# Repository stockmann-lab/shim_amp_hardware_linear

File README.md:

# MGH open-source shim amplifier repo. 

This repo contains files related to the MGH "Revision D" linear amplifier development (and associated projects).  The shim amplifiers are designed to drive stable currents (up to 4A/channel or more if channels are ganged together in parallel) in shim coils and other inductive loads used for MRI research experiments.  The amplifiers are designed to operate inside the MRI shielded room without causing image degradation due to RF interference.

Content will include design files and bills of materials for both the Printed Circuit Boards (power board, control board, and power distribution board) as well as the mechanical enclosure.

The software and firmware for controlling the shim amplifiers via a Snickerdoodle device can be built from [https://github.com/LincolnCB/rev_d_shim](https://github.com/LincolnCB/rev_d_shim) using the [https://github.com/LincolnCB/zynq_toolbox](https://github.com/LincolnCB/zynq_toolbox) build environment repo.

More details forthcoming.

## Previous shim amplifier projects 

This project builds upon previous work done at MIT-MGH on a Class-AB linear shim amplifier that uses OPA549 op amps in a push-pull configuration.  This previous "Revision C" shim amplifier design is available at:

https://rflab.martinos.org/index.php?title=Current_driver:Current_driver

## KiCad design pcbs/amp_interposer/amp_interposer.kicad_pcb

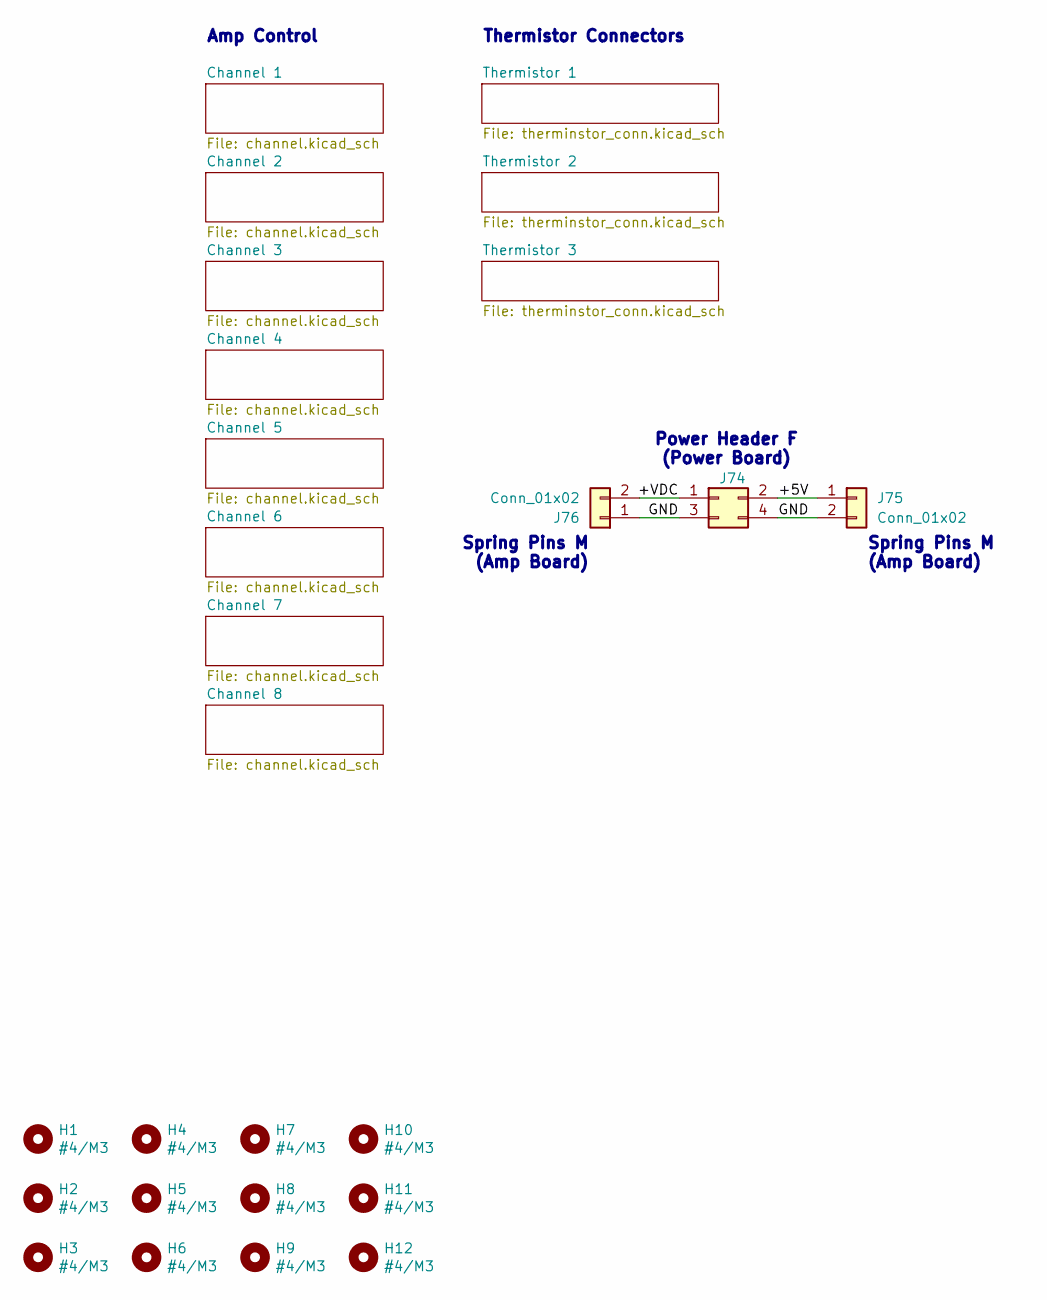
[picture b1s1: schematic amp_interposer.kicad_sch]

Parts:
H1, H2, H3, H4, H5, H6, H7, H8, H9, H10, H11, H12: #4/M3; MountingHole_3.2mm_M3
J74: Conn_02x02; PinSocket_2x02_P2.54mm_Vertical_SMD_BotEntry_Pin; MPN M20-7810245 / M20-7810245R
J75, J76: Conn_01x02; Conn_70AAJ-M_SIB_1x02_P2.54mm_M

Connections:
/+5V: J74.2, J75.1
/+VDC: J74.1, J76.2
/GND: J74.3, J74.4, J75.2, J76.1

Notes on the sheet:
Spring Pins M (Amp Board)
Power Header F (Power Board)
Thermistor Connectors
Amp Control

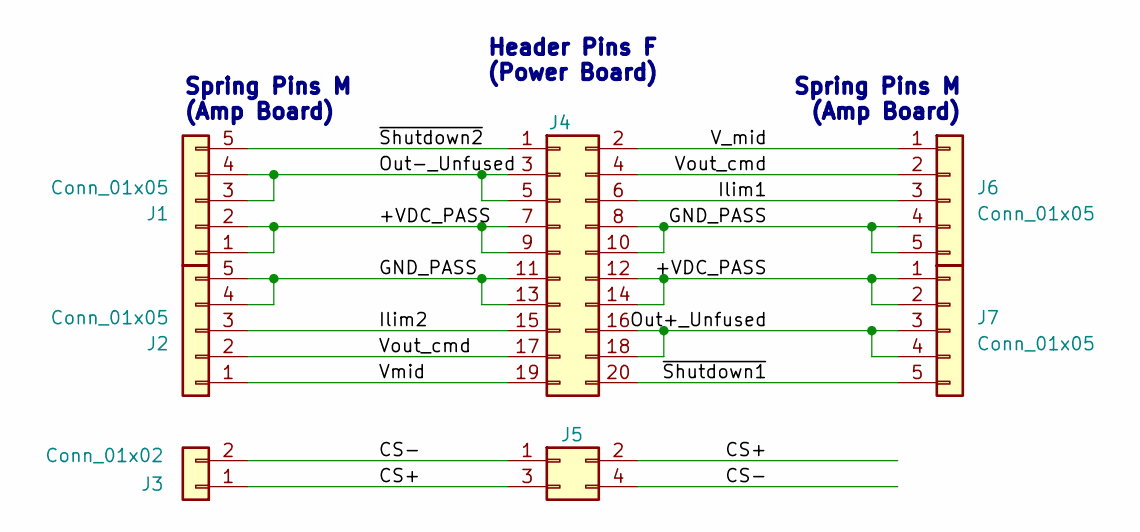
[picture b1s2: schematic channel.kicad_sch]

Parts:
J1, J2, J6, J7: Conn_01x05; Conn_70AAJ-M_SIB_1x05_P2.54mm_M
J3: Conn_01x02; Conn_70AAJ-M_SIB_1x02_P2.54mm_M
J4: Conn_02x10_Odd_Even; PinSocket_2x10_P2.54mm_Vertical_SMD_BotEntry_Pin; MPN M20-7811045 / M20-7811045R
J5: Conn_02x02; PinSocket_2x02_P2.54mm_Vertical_SMD_BotEntry_Pin; MPN M20-7810245 / M20-7810245R

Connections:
/Channel 1/+VDC_PASS: J1.1, J1.2, J4.7, J4.9, J4.12, J4.14, J7.1, J7.2
/Channel 1/CS+: J3.1, J5.2, J5.3
/Channel 1/CS-: J3.2, J5.1, J5.4
/Channel 1/GND_PASS: J2.4, J2.5, J4.8, J4.10, J4.11, J4.13, J6.4, J6.5
/Channel 1/Ilim1: J4.6, J6.3
/Channel 1/Ilim2: J2.3, J4.15
/Channel 1/Out+_Unfused: J4.16, J4.18, J7.3, J7.4
/Channel 1/Out-_Unfused: J1.3, J1.4, J4.3, J4.5
/Channel 1/V_mid: J4.2, J6.1
/Channel 1/Vmid: J2.1, J4.19
/Channel 1/Vout_cmd: J2.2, J4.4, J4.17, J6.2
/Channel 1/~Shutdown1: J4.20, J7.5
/Channel 1/~Shutdown2: J1.5, J4.1

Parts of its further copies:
J9, J10, J14, J15, J17, J18, J22, J23, J25, J26, J30, J31, J33, J34, J38, J39, J41, J42, J46, J47, J49, J50, J54, J55, J57, J58, J62, J63: Conn_01x05; Conn_70AAJ-M_SIB_1x05_P2.54mm_M
J11, J19, J27, J35, J43, J51, J59: Conn_01x02; Conn_70AAJ-M_SIB_1x02_P2.54mm_M
J12, J20, J28, J36, J44, J52, J60: Conn_02x10_Odd_Even; PinSocket_2x10_P2.54mm_Vertical_SMD_BotEntry_Pin; MPN M20-7811045 / M20-7811045R
J13, J21, J29, J37, J45, J53, J61: Conn_02x02; PinSocket_2x02_P2.54mm_Vertical_SMD_BotEntry_Pin; MPN M20-7810245 / M20-7810245R

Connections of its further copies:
/Channel 2/+VDC_PASS: J9.1, J9.2, J12.7, J12.9, J12.12, J12.14, J15.1, J15.2
/Channel 2/CS+: J11.1, J13.2, J13.3
/Channel 2/CS-: J11.2, J13.1, J13.4
/Channel 2/GND_PASS: J10.4, J10.5, J12.8, J12.10, J12.11, J12.13, J14.4, J14.5
/Channel 2/Ilim1: J12.6, J14.3
/Channel 2/Ilim2: J10.3, J12.15
/Channel 2/Out+_Unfused: J12.16, J12.18, J15.3, J15.4
/Channel 2/Out-_Unfused: J9.3, J9.4, J12.3, J12.5
/Channel 2/V_mid: J12.2, J14.1
/Channel 2/Vmid: J10.1, J12.19
/Channel 2/Vout_cmd: J10.2, J12.4, J12.17, J14.2
/Channel 2/~Shutdown1: J12.20, J15.5
/Channel 2/~Shutdown2: J9.5, J12.1
/Channel 3/+VDC_PASS: J17.1, J17.2, J20.7, J20.9, J20.12, J20.14, J23.1, J23.2
/Channel 3/CS+: J19.1, J21.2, J21.3
/Channel 3/CS-: J19.2, J21.1, J21.4
/Channel 3/GND_PASS: J18.4, J18.5, J20.8, J20.10, J20.11, J20.13, J22.4, J22.5
/Channel 3/Ilim1: J20.6, J22.3
/Channel 3/Ilim2: J18.3, J20.15
/Channel 3/Out+_Unfused: J20.16, J20.18, J23.3, J23.4
/Channel 3/Out-_Unfused: J17.3, J17.4, J20.3, J20.5
/Channel 3/V_mid: J20.2, J22.1
/Channel 3/Vmid: J18.1, J20.19
/Channel 3/Vout_cmd: J18.2, J20.4, J20.17, J22.2
/Channel 3/~Shutdown1: J20.20, J23.5
/Channel 3/~Shutdown2: J17.5, J20.1
/Channel 4/+VDC_PASS: J25.1, J25.2, J28.7, J28.9, J28.12, J28.14, J31.1, J31.2
/Channel 4/CS+: J27.1, J29.2, J29.3
/Channel 4/CS-: J27.2, J29.1, J29.4
/Channel 4/GND_PASS: J26.4, J26.5, J28.8, J28.10, J28.11, J28.13, J30.4, J30.5
/Channel 4/Ilim1: J28.6, J30.3
/Channel 4/Ilim2: J26.3, J28.15
/Channel 4/Out+_Unfused: J28.16, J28.18, J31.3, J31.4
/Channel 4/Out-_Unfused: J25.3, J25.4, J28.3, J28.5
/Channel 4/V_mid: J28.2, J30.1
/Channel 4/Vmid: J26.1, J28.19
/Channel 4/Vout_cmd: J26.2, J28.4, J28.17, J30.2
/Channel 4/~Shutdown1: J28.20, J31.5
/Channel 4/~Shutdown2: J25.5, J28.1
/Channel 5/+VDC_PASS: J33.1, J33.2, J36.7, J36.9, J36.12, J36.14, J39.1, J39.2
/Channel 5/CS+: J35.1, J37.2, J37.3
/Channel 5/CS-: J35.2, J37.1, J37.4
/Channel 5/GND_PASS: J34.4, J34.5, J36.8, J36.10, J36.11, J36.13, J38.4, J38.5
/Channel 5/Ilim1: J36.6, J38.3
/Channel 5/Ilim2: J34.3, J36.15
/Channel 5/Out+_Unfused: J36.16, J36.18, J39.3, J39.4
/Channel 5/Out-_Unfused: J33.3, J33.4, J36.3, J36.5
/Channel 5/V_mid: J36.2, J38.1
/Channel 5/Vmid: J34.1, J36.19
/Channel 5/Vout_cmd: J34.2, J36.4, J36.17, J38.2
/Channel 5/~Shutdown1: J36.20, J39.5
/Channel 5/~Shutdown2: J33.5, J36.1
/Channel 6/+VDC_PASS: J41.1, J41.2, J44.7, J44.9, J44.12, J44.14, J47.1, J47.2
/Channel 6/CS+: J43.1, J45.2, J45.3
/Channel 6/CS-: J43.2, J45.1, J45.4
/Channel 6/GND_PASS: J42.4, J42.5, J44.8, J44.10, J44.11, J44.13, J46.4, J46.5
/Channel 6/Ilim1: J44.6, J46.3
/Channel 6/Ilim2: J42.3, J44.15
/Channel 6/Out+_Unfused: J44.16, J44.18, J47.3, J47.4
/Channel 6/Out-_Unfused: J41.3, J41.4, J44.3, J44.5
/Channel 6/V_mid: J44.2, J46.1
/Channel 6/Vmid: J42.1, J44.19
/Channel 6/Vout_cmd: J42.2, J44.4, J44.17, J46.2
/Channel 6/~Shutdown1: J44.20, J47.5
/Channel 6/~Shutdown2: J41.5, J44.1
/Channel 7/+VDC_PASS: J49.1, J49.2, J52.7, J52.9, J52.12, J52.14, J55.1, J55.2
/Channel 7/CS+: J51.1, J53.2, J53.3
/Channel 7/CS-: J51.2, J53.1, J53.4
/Channel 7/GND_PASS: J50.4, J50.5, J52.8, J52.10, J52.11, J52.13, J54.4, J54.5
/Channel 7/Ilim1: J52.6, J54.3
/Channel 7/Ilim2: J50.3, J52.15
/Channel 7/Out+_Unfused: J52.16, J52.18, J55.3, J55.4
/Channel 7/Out-_Unfused: J49.3, J49.4, J52.3, J52.5
/Channel 7/V_mid: J52.2, J54.1
/Channel 7/Vmid: J50.1, J52.19
/Channel 7/Vout_cmd: J50.2, J52.4, J52.17, J54.2
/Channel 7/~Shutdown1: J52.20, J55.5
/Channel 7/~Shutdown2: J49.5, J52.1
/Channel 8/+VDC_PASS: J57.1, J57.2, J60.7, J60.9, J60.12, J60.14, J63.1, J63.2
/Channel 8/CS+: J59.1, J61.2, J61.3
/Channel 8/CS-: J59.2, J61.1, J61.4
/Channel 8/GND_PASS: J58.4, J58.5, J60.8, J60.10, J60.11, J60.13, J62.4, J62.5
/Channel 8/Ilim1: J60.6, J62.3
/Channel 8/Ilim2: J58.3, J60.15
/Channel 8/Out+_Unfused: J60.16, J60.18, J63.3, J63.4
/Channel 8/Out-_Unfused: J57.3, J57.4, J60.3, J60.5
/Channel 8/V_mid: J60.2, J62.1
/Channel 8/Vmid: J58.1, J60.19
/Channel 8/Vout_cmd: J58.2, J60.4, J60.17, J62.2
/Channel 8/~Shutdown1: J60.20, J63.5
/Channel 8/~Shutdown2: J57.5, J60.1

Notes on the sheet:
Spring Pins M (Amp Board)
Header Pins F (Power Board)

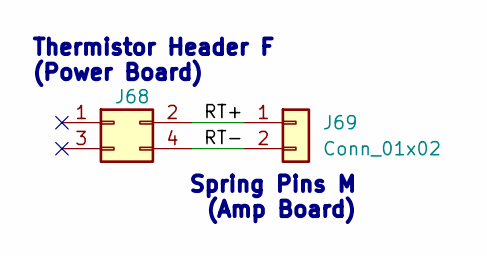
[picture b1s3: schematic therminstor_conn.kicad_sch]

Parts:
J68: Conn_02x02; PinSocket_2x02_P2.54mm_Vertical_SMD_BotEntry_Pin; MPN M20-7810245 / M20-7810245R
J69: Conn_01x02; Conn_70AAJ-M_SIB_1x02_P2.54mm_M

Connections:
/Thermistor 1/RT+: J68.2, J69.1
/Thermistor 1/RT-: J68.4, J69.2

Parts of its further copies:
J70, J72: Conn_02x02; PinSocket_2x02_P2.54mm_Vertical_SMD_BotEntry_Pin; MPN M20-7810245 / M20-7810245R
J71, J73: Conn_01x02; Conn_70AAJ-M_SIB_1x02_P2.54mm_M

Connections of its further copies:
/Thermistor 2/RT+: J70.2, J71.1
/Thermistor 2/RT-: J70.4, J71.2
/Thermistor 3/RT+: J72.2, J73.1
/Thermistor 3/RT-: J72.4, J73.2

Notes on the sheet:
Thermistor Header F (Power Board)
Spring Pins M (Amp Board)

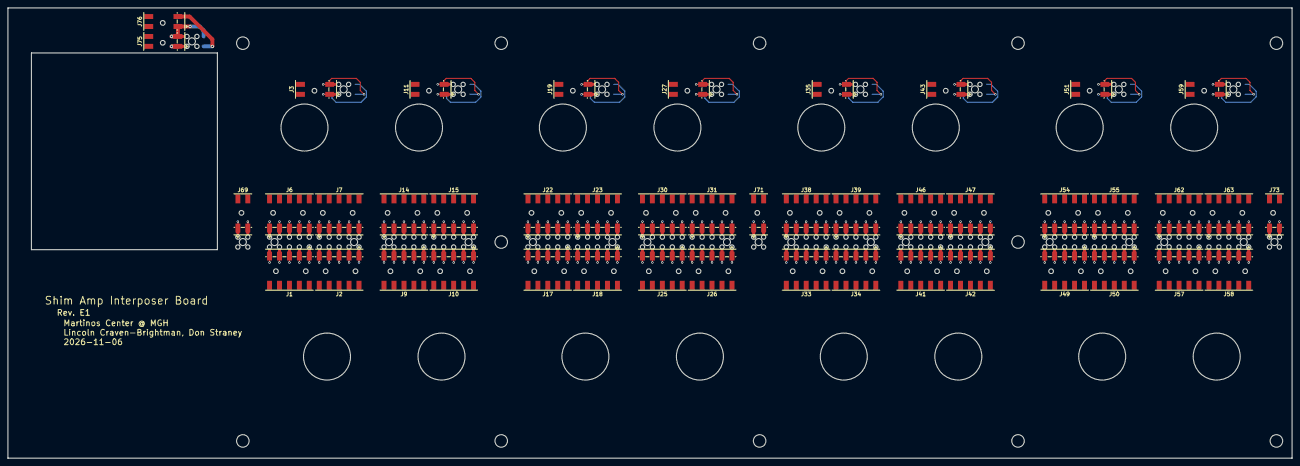
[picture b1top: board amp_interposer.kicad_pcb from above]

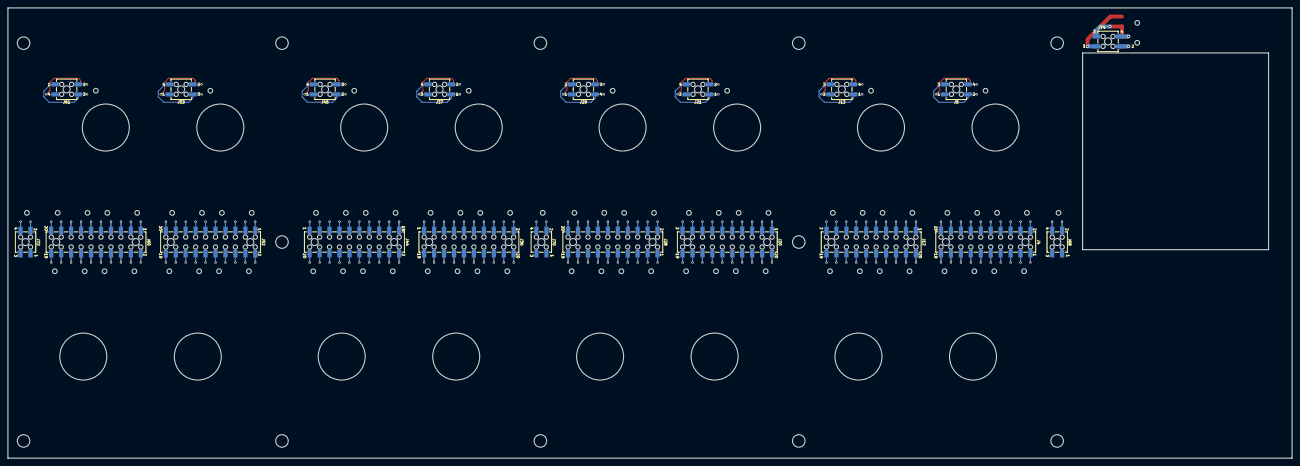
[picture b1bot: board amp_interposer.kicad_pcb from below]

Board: 2 copper layers, 328.0 x 115.0 mm, 77 parts (20 on the bottom side), 113 nets.

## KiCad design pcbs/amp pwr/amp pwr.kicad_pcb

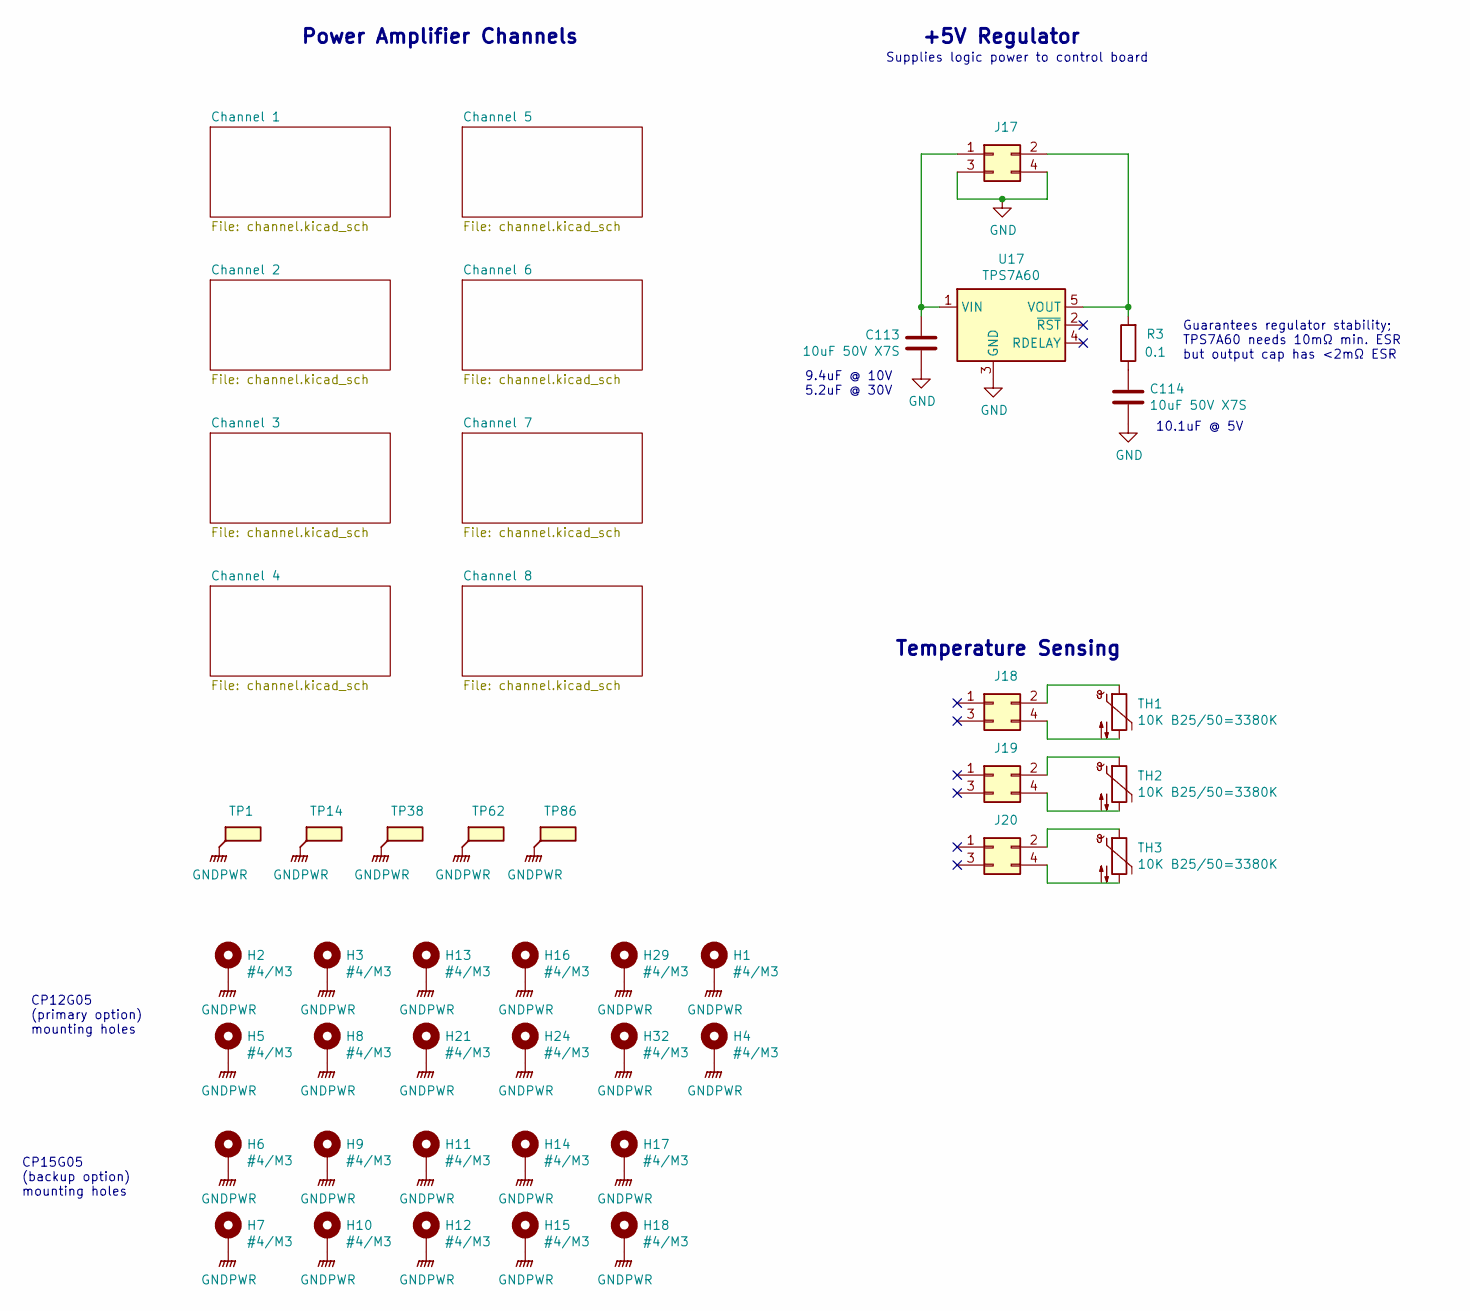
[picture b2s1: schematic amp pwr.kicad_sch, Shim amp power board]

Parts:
C113, C114: 10uF 50V X7S; C_1210_3225Metric; Part Number GCM32EC71H106KA03
H1, H2, H3, H4, H5, H6, H7, H8, H9, H10, H11, H12, H13, H14, H15, H16, H17, H18, H21, H24, H29, H32: #4/M3; MountingHole_3.2mm_M3_DIN965_Pad
J17, J18, J19, J20: Conn_02x02_Odd_Even; PinHeader_2x02_P2.54mm_Vertical_SMD; Part Number TSM-102-03-L-DV
R3: 0.1; R_0805_2012Metric; Part Number RL1220S-R10-F
TH1, TH2, TH3: 10K B25/50=3380K; R_0603_1608Metric; Part Number ERT-J1VG103FA
TP1, TP14, TP38, TP62, TP86: TestPoint_Flag; TestPoint_Keystone_5019_Miniature; Part Number 5019
U17: TPS7A60; TO-252-5_TabPin3; Part Number TPS7A6050QKVURQ1

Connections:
GND: C113.2, C114.2, J17.3, J17.4, U17.3 (GND)
GNDPWR: H1.1 (1_1), H2.1 (1_1), H3.1 (1_1), H4.1 (1_1), H5.1 (1_1), H6.1 (1_1), H7.1 (1_1), H8.1 (1_1), H9.1 (1_1), H10.1 (1_1), H11.1 (1_1), H12.1 (1_1), H13.1 (1_1), H14.1 (1_1), H15.1 (1_1), H16.1 (1_1), H17.1 (1_1), H18.1 (1_1), H21.1 (1_1), H24.1 (1_1), H29.1 (1_1), H32.1 (1_1), TP1.1 (1_1), TP14.1 (1_1), TP38.1 (1_1), TP62.1 (1_1), TP86.1 (1_1); also elsewhere on the board
unnamed: C114.1, R3.1
unnamed: C113.1, J17.1, U17.1 (VIN)
unnamed: J17.2, R3.2, U17.5 (VOUT)
unnamed: J18.2, TH1.1
unnamed: J18.4, TH1.2
unnamed: J19.2, TH2.1
unnamed: J19.4, TH2.2
unnamed: J20.2, TH3.1
unnamed: J20.4, TH3.2

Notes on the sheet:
Temperature Sensing
CP12G05 (primary option) mounting holes
10.1uF @ 5V
Power Amplifier Channels
+5V Regulator
Guarantees regulator stability; TPS7A60 needs 10mΩ min. ESR but output cap has <2mΩ ESR
9.4uF @ 10V 5.2uF @ 30V
CP15G05 (backup option) mounting holes
Supplies logic power to control board

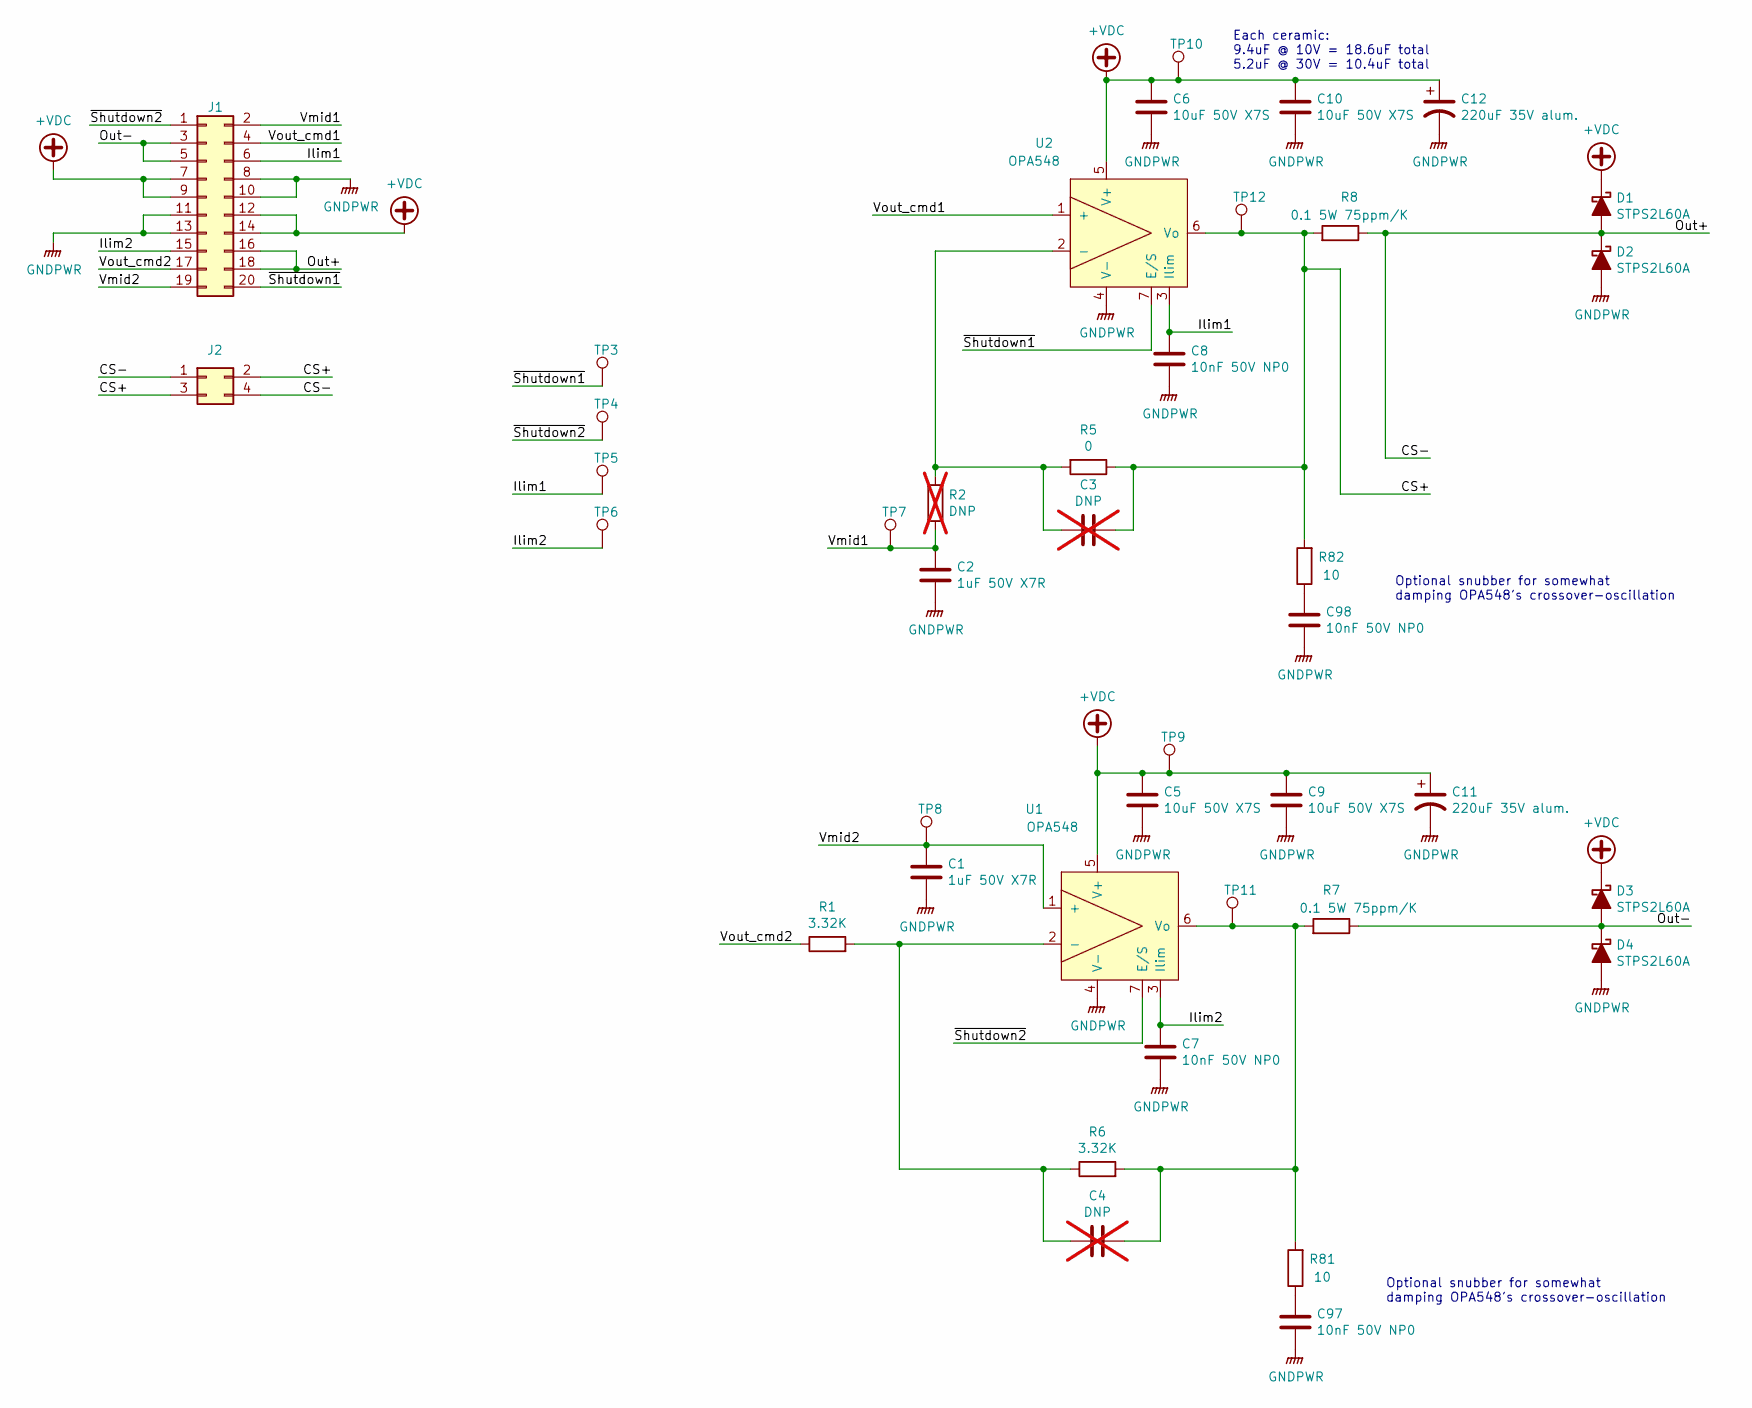
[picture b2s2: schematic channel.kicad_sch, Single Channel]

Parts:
C1, C2: 1uF 50V X7R; C_1206_3216Metric; Part Number C1206C105K5RACTU
C3, C4: DNP; C_0805_2012Metric; not fitted
C5, C6, C9, C10: 10uF 50V X7S; C_1210_3225Metric; Part Number GCM32EC71H106KA03
C7, C8, C97, C98: 10nF 50V NP0; C_0603_1608Metric; Part Number GRM1885C1H103JA01D
C11, C12: 220uF 35V alum.; CP_Elec_8x6.9; Part Number PCR1V221MCL1GS
D1, D2, D3, D4: STPS2L60A; D_SMA; Part Number STPS2L60A
J1: Conn_02x10_Odd_Even; PinHeader_2x10_P2.54mm_Vertical_SMD; Part Number TSM-110-03-L-DV
J2: Conn_02x02_Odd_Even; PinHeader_2x02_P2.54mm_Vertical_SMD; Part Number TSM-102-03-L-DV
R1, R6: 3.32K; R_1206_3216Metric; Part Number RK73H2BTTD3321F
R2: DNP; R_1206_3216Metric; not fitted
R5: 0; R_1206_3216Metric; Part Number CRCW12060000Z0EBC
R7, R8: 0.1 5W 75ppm/K; R_Shunt_Vishay_WSR5; Part Number WSR5R1000F
R81, R82: 10; R_1206_3216Metric; Part Number RK73H2BTTE10R0F
TP3, TP4, TP5, TP6, TP7, TP8, TP9, TP10, TP11, TP12: TestPoint; TestPoint_Pad_D1.5mm
U1, U2: OPA548; TO-263-7_TabPin4; Part Number OPA548F/500

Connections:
+VDC: C5.1, C6.1, C9.1, C10.1, C11.1, C12.1, D1.1 (K), D3.1 (K), J1.7, J1.9, J1.12, J1.14, TP9.1 (1_1), TP10.1 (1_1), U1.5 (V+), U2.5 (V+); also elsewhere on the board
/Channel 1/CS+: C3.1, J2.2, J2.3, R5.1, R8.2, R82.2, TP12.1 (1_1), U2.6 (Vo)
/Channel 1/CS-: D1.2 (A), D2.1 (K), J1.16, J1.18, J2.1, J2.4, R8.1
/Channel 1/Ilim1: C8.1, J1.6, TP5.1 (1_1), U2.3 (Ilim)
/Channel 1/Ilim2: C7.1, J1.15, TP6.1 (1_1), U1.3 (Ilim)
/Channel 1/Out-: D3.2 (A), D4.1 (K), J1.3, J1.5, R7.1
/Channel 1/Vmid1: C2.2, J1.2, R2.1, TP7.1 (1_1)
/Channel 1/Vmid2: C1.2, J1.19, TP8.1 (1_1), U1.1 (+)
/Channel 1/Vout_cmd1: J1.4, U2.1 (+)
/Channel 1/Vout_cmd2: J1.17, R1.1
/Channel 1/~Shutdown1: J1.20, TP3.1 (1_1), U2.7 (E/S)
/Channel 1/~Shutdown2: J1.1, TP4.1 (1_1), U1.7 (E/S)
GNDPWR: C1.1, C2.1, C5.2, C6.2, C7.2, C8.2, C9.2, C10.2, C11.2, C12.2, C97.2, C98.2, D2.2 (A), D4.2 (A), J1.8, J1.10, J1.11, J1.13, U1.4 (V-), U2.4 (V-); also elsewhere on the board
unnamed: C97.1, R81.1
unnamed: C98.1, R82.1
unnamed: C4.2, R1.2, R6.1, U1.2 (-)
unnamed: C4.1, R6.2, R7.2, R81.2, TP11.1 (1_1), U1.6 (Vo)
unnamed: C3.2, R2.2, R5.2, U2.2 (-)

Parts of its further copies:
C13, C14, C25, C26, C37, C38, C49, C50, C61, C62, C73, C74, C85, C86: 1uF 50V X7R; C_1206_3216Metric; Part Number C1206C105K5RACTU
C15, C16, C27, C28, C39, C40, C51, C52, C63, C64, C75, C76, C87, C88: DNP; C_0805_2012Metric; not fitted
C17, C18, C21, C22, C29, C30, C33, C34, C41, C42, C45, C46, C53, C54, C57, C58, C65, C66, C69, C70, C77, C78, C81, C82, C89, C90, C93, C94: 10uF 50V X7S; C_1210_3225Metric; Part Number GCM32EC71H106KA03
C19, C20, C31, C32, C43, C44, C55, C56, C67, C68, C79, C80, C91, C92, C99, C100, C101, C102, C103, C104, C105, C106, C107, C108, C109, C110, C111, C112: 10nF 50V NP0; C_0603_1608Metric; Part Number GRM1885C1H103JA01D
C23, C24, C35, C36, C47, C48, C59, C60, C71, C72, C83, C84, C95, C96: 220uF 35V alum.; CP_Elec_8x6.9; Part Number PCR1V221MCL1GS
D5, D6, D7, D8, D9, D10, D11, D12, D13, D14, D15, D16, D17, D18, D19, D20, D21, D22, D23, D24, D25, D26, D27, D28, D29, D30, D31, D32: STPS2L60A; D_SMA; Part Number STPS2L60A
J3, J5, J7, J9, J11, J13, J15: Conn_02x10_Odd_Even; PinHeader_2x10_P2.54mm_Vertical_SMD; Part Number TSM-110-03-L-DV
J4, J6, J8, J10, J12, J14, J16: Conn_02x02_Odd_Even; PinHeader_2x02_P2.54mm_Vertical_SMD; Part Number TSM-102-03-L-DV
R11, R16, R21, R26, R31, R36, R41, R46, R51, R56, R61, R66, R71, R76: 3.32K; R_1206_3216Metric; Part Number RK73H2BTTD3321F
R12, R22, R32, R42, R52, R62, R72: DNP; R_1206_3216Metric; not fitted
R15, R25, R35, R45, R55, R65, R75: 0; R_1206_3216Metric; Part Number CRCW12060000Z0EBC
R17, R18, R27, R28, R37, R38, R47, R48, R57, R58, R67, R68, R77, R78: 0.1 5W 75ppm/K; R_Shunt_Vishay_WSR5; Part Number WSR5R1000F
R83, R84, R85, R86, R87, R88, R89, R90, R91, R92, R93, R94, R95, R96: 10; R_1206_3216Metric; Part Number RK73H2BTTE10R0F
TP15, TP16, TP17, TP18, TP19, TP20, TP21, TP22, TP23, TP24, TP27, TP28, TP29, TP30, TP31, TP32, TP33, TP34, TP35, TP36, TP39, TP40, TP41, TP42, TP43, TP44, TP45, TP46, TP47, TP48, TP51, TP52, TP53, TP54, TP55, TP56, TP57, TP58, TP59, TP60, TP63, TP64, TP65, TP66, TP67, TP68, TP69, TP70, TP71, TP72, TP75, TP76, TP77, TP78, TP79, TP80, TP81, TP82, TP83, TP84, TP87, TP88, TP89, TP90, TP91, TP92, TP93, TP94, TP95, TP96: TestPoint; TestPoint_Pad_D1.5mm
U3, U4, U5, U6, U7, U8, U9, U10, U11, U12, U13, U14, U15, U16: OPA548; TO-263-7_TabPin4; Part Number OPA548F/500

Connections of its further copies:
+VDC: C17.1, C18.1, C21.1, C22.1, C23.1, C24.1, C29.1, C30.1, C33.1, C34.1, C35.1, C36.1, C41.1, C42.1, C45.1, C46.1, C47.1, C48.1, C53.1, C54.1, C57.1, C58.1, C59.1, C60.1, C65.1, C66.1, C69.1, C70.1, C71.1, C72.1, C77.1, C78.1, C81.1, C82.1, C83.1, C84.1, C89.1, C90.1, C93.1, C94.1, C95.1, C96.1, D5.1 (K), D7.1 (K), D9.1 (K), D11.1 (K), D13.1 (K), D15.1 (K), D17.1 (K), D19.1 (K), D21.1 (K), D23.1 (K), D25.1 (K), D27.1 (K), D29.1 (K), D31.1 (K), J3.7, J3.9, J3.12, J3.14, J5.7, J5.9, J5.12, J5.14, J7.7, J7.9, J7.12, J7.14, J9.7, J9.9, J9.12, J9.14, J11.7, J11.9, J11.12, J11.14, J13.7, J13.9, J13.12, J13.14, J15.7, J15.9, J15.12, J15.14, TP21.1 (1_1), TP22.1 (1_1), TP33.1 (1_1), TP34.1 (1_1), TP45.1 (1_1), TP46.1 (1_1), TP57.1 (1_1), TP58.1 (1_1), TP69.1 (1_1), TP70.1 (1_1), TP81.1 (1_1), TP82.1 (1_1), TP93.1 (1_1), TP94.1 (1_1), U3.5 (V+), U4.5 (V+), U5.5 (V+), U6.5 (V+), U7.5 (V+), U8.5 (V+), U9.5 (V+), U10.5 (V+), U11.5 (V+), U12.5 (V+), U13.5 (V+), U14.5 (V+), U15.5 (V+), U16.5 (V+); also elsewhere on the board
/Channel 2/CS+: C15.1, J4.2, J4.3, R15.1, R18.2, R84.2, TP24.1 (1_1), U4.6 (Vo)
/Channel 2/CS-: D5.2 (A), D6.1 (K), J3.16, J3.18, J4.1, J4.4, R18.1
/Channel 2/Ilim1: C20.1, J3.6, TP17.1 (1_1), U4.3 (Ilim)
/Channel 2/Ilim2: C19.1, J3.15, TP18.1 (1_1), U3.3 (Ilim)
/Channel 2/Out-: D7.2 (A), D8.1 (K), J3.3, J3.5, R17.1
/Channel 2/Vmid1: C14.2, J3.2, R12.1, TP19.1 (1_1)
/Channel 2/Vmid2: C13.2, J3.19, TP20.1 (1_1), U3.1 (+)
/Channel 2/Vout_cmd1: J3.4, U4.1 (+)
/Channel 2/Vout_cmd2: J3.17, R11.1
/Channel 2/~Shutdown1: J3.20, TP15.1 (1_1), U4.7 (E/S)
/Channel 2/~Shutdown2: J3.1, TP16.1 (1_1), U3.7 (E/S)
/Channel 3/CS+: C27.1, J6.2, J6.3, R25.1, R28.2, R86.2, TP36.1 (1_1), U6.6 (Vo)
/Channel 3/CS-: D9.2 (A), D10.1 (K), J5.16, J5.18, J6.1, J6.4, R28.1
/Channel 3/Ilim1: C32.1, J5.6, TP29.1 (1_1), U6.3 (Ilim)
/Channel 3/Ilim2: C31.1, J5.15, TP30.1 (1_1), U5.3 (Ilim)
/Channel 3/Out-: D11.2 (A), D12.1 (K), J5.3, J5.5, R27.1
/Channel 3/Vmid1: C26.2, J5.2, R22.1, TP31.1 (1_1)
/Channel 3/Vmid2: C25.2, J5.19, TP32.1 (1_1), U5.1 (+)
/Channel 3/Vout_cmd1: J5.4, U6.1 (+)
/Channel 3/Vout_cmd2: J5.17, R21.1
/Channel 3/~Shutdown1: J5.20, TP27.1 (1_1), U6.7 (E/S)
/Channel 3/~Shutdown2: J5.1, TP28.1 (1_1), U5.7 (E/S)
/Channel 4/CS+: C39.1, J8.2, J8.3, R35.1, R38.2, R88.2, TP48.1 (1_1), U8.6 (Vo)
/Channel 4/CS-: D13.2 (A), D14.1 (K), J7.16, J7.18, J8.1, J8.4, R38.1
/Channel 4/Ilim1: C44.1, J7.6, TP41.1 (1_1), U8.3 (Ilim)
/Channel 4/Ilim2: C43.1, J7.15, TP42.1 (1_1), U7.3 (Ilim)
/Channel 4/Out-: D15.2 (A), D16.1 (K), J7.3, J7.5, R37.1
/Channel 4/Vmid1: C38.2, J7.2, R32.1, TP43.1 (1_1)
/Channel 4/Vmid2: C37.2, J7.19, TP44.1 (1_1), U7.1 (+)
/Channel 4/Vout_cmd1: J7.4, U8.1 (+)
/Channel 4/Vout_cmd2: J7.17, R31.1
/Channel 4/~Shutdown1: J7.20, TP39.1 (1_1), U8.7 (E/S)
/Channel 4/~Shutdown2: J7.1, TP40.1 (1_1), U7.7 (E/S)
/Channel 5/CS+: C51.1, J10.2, J10.3, R45.1, R48.2, R90.2, TP60.1 (1_1), U10.6 (Vo)
/Channel 5/CS-: D17.2 (A), D18.1 (K), J9.16, J9.18, J10.1, J10.4, R48.1
/Channel 5/Ilim1: C56.1, J9.6, TP53.1 (1_1), U10.3 (Ilim)
/Channel 5/Ilim2: C55.1, J9.15, TP54.1 (1_1), U9.3 (Ilim)
/Channel 5/Out-: D19.2 (A), D20.1 (K), J9.3, J9.5, R47.1
/Channel 5/Vmid1: C50.2, J9.2, R42.1, TP55.1 (1_1)
/Channel 5/Vmid2: C49.2, J9.19, TP56.1 (1_1), U9.1 (+)
/Channel 5/Vout_cmd1: J9.4, U10.1 (+)
/Channel 5/Vout_cmd2: J9.17, R41.1
/Channel 5/~Shutdown1: J9.20, TP51.1 (1_1), U10.7 (E/S)
/Channel 5/~Shutdown2: J9.1, TP52.1 (1_1), U9.7 (E/S)
/Channel 6/CS+: C63.1, J12.2, J12.3, R55.1, R58.2, R92.2, TP72.1 (1_1), U12.6 (Vo)
/Channel 6/CS-: D21.2 (A), D22.1 (K), J11.16, J11.18, J12.1, J12.4, R58.1
/Channel 6/Ilim1: C68.1, J11.6, TP65.1 (1_1), U12.3 (Ilim)
/Channel 6/Ilim2: C67.1, J11.15, TP66.1 (1_1), U11.3 (Ilim)
/Channel 6/Out-: D23.2 (A), D24.1 (K), J11.3, J11.5, R57.1
/Channel 6/Vmid1: C62.2, J11.2, R52.1, TP67.1 (1_1)
/Channel 6/Vmid2: C61.2, J11.19, TP68.1 (1_1), U11.1 (+)
/Channel 6/Vout_cmd1: J11.4, U12.1 (+)
/Channel 6/Vout_cmd2: J11.17, R51.1
/Channel 6/~Shutdown1: J11.20, TP63.1 (1_1), U12.7 (E/S)
/Channel 6/~Shutdown2: J11.1, TP64.1 (1_1), U11.7 (E/S)
/Channel 7/CS+: C75.1, J14.2, J14.3, R65.1, R68.2, R94.2, TP84.1 (1_1), U14.6 (Vo)
/Channel 7/CS-: D25.2 (A), D26.1 (K), J13.16, J13.18, J14.1, J14.4, R68.1
/Channel 7/Ilim1: C80.1, J13.6, TP77.1 (1_1), U14.3 (Ilim)
/Channel 7/Ilim2: C79.1, J13.15, TP78.1 (1_1), U13.3 (Ilim)
/Channel 7/Out-: D27.2 (A), D28.1 (K), J13.3, J13.5, R67.1
/Channel 7/Vmid1: C74.2, J13.2, R62.1, TP79.1 (1_1)
/Channel 7/Vmid2: C73.2, J13.19, TP80.1 (1_1), U13.1 (+)
/Channel 7/Vout_cmd1: J13.4, U14.1 (+)
/Channel 7/Vout_cmd2: J13.17, R61.1
/Channel 7/~Shutdown1: J13.20, TP75.1 (1_1), U14.7 (E/S)
/Channel 7/~Shutdown2: J13.1, TP76.1 (1_1), U13.7 (E/S)
/Channel 8/CS+: C87.1, J16.2, J16.3, R75.1, R78.2, R96.2, TP96.1 (1_1), U16.6 (Vo)
/Channel 8/CS-: D29.2 (A), D30.1 (K), J15.16, J15.18, J16.1, J16.4, R78.1
/Channel 8/Ilim1: C92.1, J15.6, TP89.1 (1_1), U16.3 (Ilim)
/Channel 8/Ilim2: C91.1, J15.15, TP90.1 (1_1), U15.3 (Ilim)
/Channel 8/Out-: D31.2 (A), D32.1 (K), J15.3, J15.5, R77.1
/Channel 8/Vmid1: C86.2, J15.2, R72.1, TP91.1 (1_1)
/Channel 8/Vmid2: C85.2, J15.19, TP92.1 (1_1), U15.1 (+)
/Channel 8/Vout_cmd1: J15.4, U16.1 (+)
/Channel 8/Vout_cmd2: J15.17, R71.1
/Channel 8/~Shutdown1: J15.20, TP87.1 (1_1), U16.7 (E/S)
/Channel 8/~Shutdown2: J15.1, TP88.1 (1_1), U15.7 (E/S)
GNDPWR: C13.1, C14.1, C17.2, C18.2, C19.2, C20.2, C21.2, C22.2, C23.2, C24.2, C25.1, C26.1, C29.2, C30.2, C31.2, C32.2, C33.2, C34.2, C35.2, C36.2, C37.1, C38.1, C41.2, C42.2, C43.2, C44.2, C45.2, C46.2, C47.2, C48.2, C49.1, C50.1, C53.2, C54.2, C55.2, C56.2, C57.2, C58.2, C59.2, C60.2, C61.1, C62.1, C65.2, C66.2, C67.2, C68.2, C69.2, C70.2, C71.2, C72.2, C73.1, C74.1, C77.2, C78.2, C79.2, C80.2, C81.2, C82.2, C83.2, C84.2, C85.1, C86.1, C89.2, C90.2, C91.2, C92.2, C93.2, C94.2, C95.2, C96.2, C99.2, C100.2, C101.2, C102.2, C103.2, C104.2, C105.2, C106.2, C107.2, C108.2, C109.2, C110.2, C111.2, C112.2, D6.2 (A), D8.2 (A), D10.2 (A), D12.2 (A), D14.2 (A), D16.2 (A), D18.2 (A), D20.2 (A), D22.2 (A), D24.2 (A), D26.2 (A), D28.2 (A), D30.2 (A), D32.2 (A), J3.8, J3.10, J3.11, J3.13, J5.8, J5.10, J5.11, J5.13, J7.8, J7.10, J7.11, J7.13, J9.8, J9.10, J9.11, J9.13, J11.8, J11.10, J11.11, J11.13, J13.8, J13.10, J13.11, J13.13, J15.8, J15.10, J15.11, J15.13, U3.4 (V-), U4.4 (V-), U5.4 (V-), U6.4 (V-), U7.4 (V-), U8.4 (V-), U9.4 (V-), U10.4 (V-), U11.4 (V-), U12.4 (V-), U13.4 (V-), U14.4 (V-), U15.4 (V-), U16.4 (V-); also elsewhere on the board
unnamed: C99.1, R83.1
unnamed: C100.1, R84.1
unnamed: C101.1, R85.1
unnamed: C102.1, R86.1
unnamed: C103.1, R87.1
unnamed: C104.1, R88.1
unnamed: C105.1, R89.1
unnamed: C106.1, R90.1
unnamed: C107.1, R91.1
unnamed: C108.1, R92.1
unnamed: C109.1, R93.1
unnamed: C110.1, R94.1
unnamed: C111.1, R95.1
unnamed: C112.1, R96.1
unnamed: C16.2, R11.2, R16.1, U3.2 (-)
unnamed: C16.1, R16.2, R17.2, R83.2, TP23.1 (1_1), U3.6 (Vo)
unnamed: C15.2, R12.2, R15.2, U4.2 (-)
unnamed: C28.2, R21.2, R26.1, U5.2 (-)
unnamed: C28.1, R26.2, R27.2, R85.2, TP35.1 (1_1), U5.6 (Vo)
unnamed: C27.2, R22.2, R25.2, U6.2 (-)
unnamed: C40.2, R31.2, R36.1, U7.2 (-)
unnamed: C40.1, R36.2, R37.2, R87.2, TP47.1 (1_1), U7.6 (Vo)
unnamed: C39.2, R32.2, R35.2, U8.2 (-)
unnamed: C52.2, R41.2, R46.1, U9.2 (-)
unnamed: C52.1, R46.2, R47.2, R89.2, TP59.1 (1_1), U9.6 (Vo)
unnamed: C51.2, R42.2, R45.2, U10.2 (-)
unnamed: C64.2, R51.2, R56.1, U11.2 (-)
unnamed: C64.1, R56.2, R57.2, R91.2, TP71.1 (1_1), U11.6 (Vo)
unnamed: C63.2, R52.2, R55.2, U12.2 (-)
unnamed: C76.2, R61.2, R66.1, U13.2 (-)
unnamed: C76.1, R66.2, R67.2, R93.2, TP83.1 (1_1), U13.6 (Vo)
unnamed: C75.2, R62.2, R65.2, U14.2 (-)
unnamed: C88.2, R71.2, R76.1, U15.2 (-)
unnamed: C88.1, R76.2, R77.2, R95.2, TP95.1 (1_1), U15.6 (Vo)
unnamed: C87.2, R72.2, R75.2, U16.2 (-)

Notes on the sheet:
Optional snubber for somewhat damping OPA548's crossover-oscillation
Each ceramic: 9.4uF @ 10V = 18.6uF total 5.2uF @ 30V = 10.4uF total

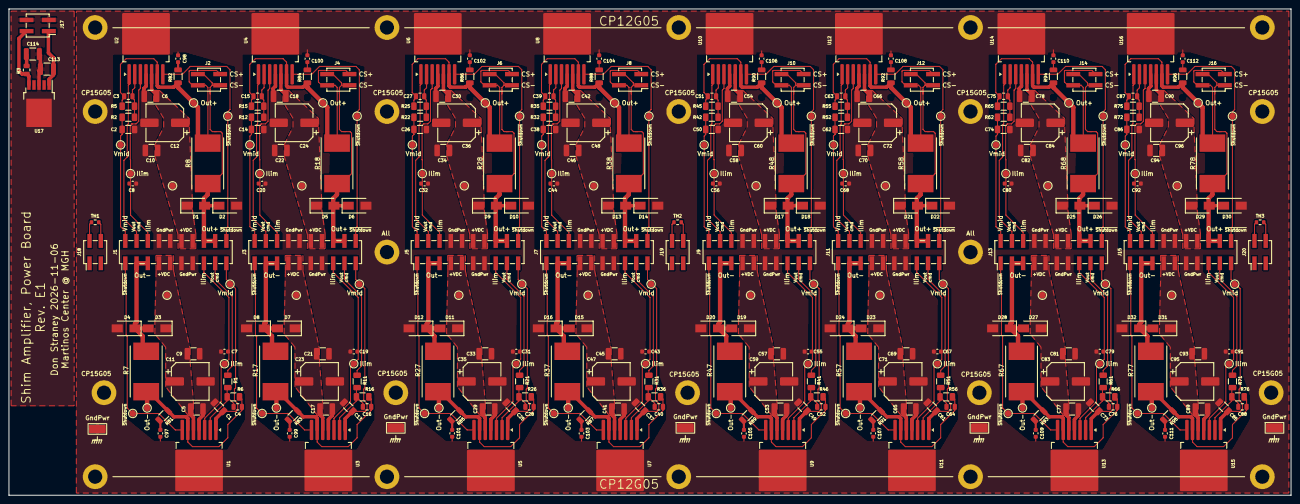
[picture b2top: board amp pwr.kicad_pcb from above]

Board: 2 copper layers, 290.0 x 110.0 mm, 358 parts (0 on the bottom side), 140 nets.
